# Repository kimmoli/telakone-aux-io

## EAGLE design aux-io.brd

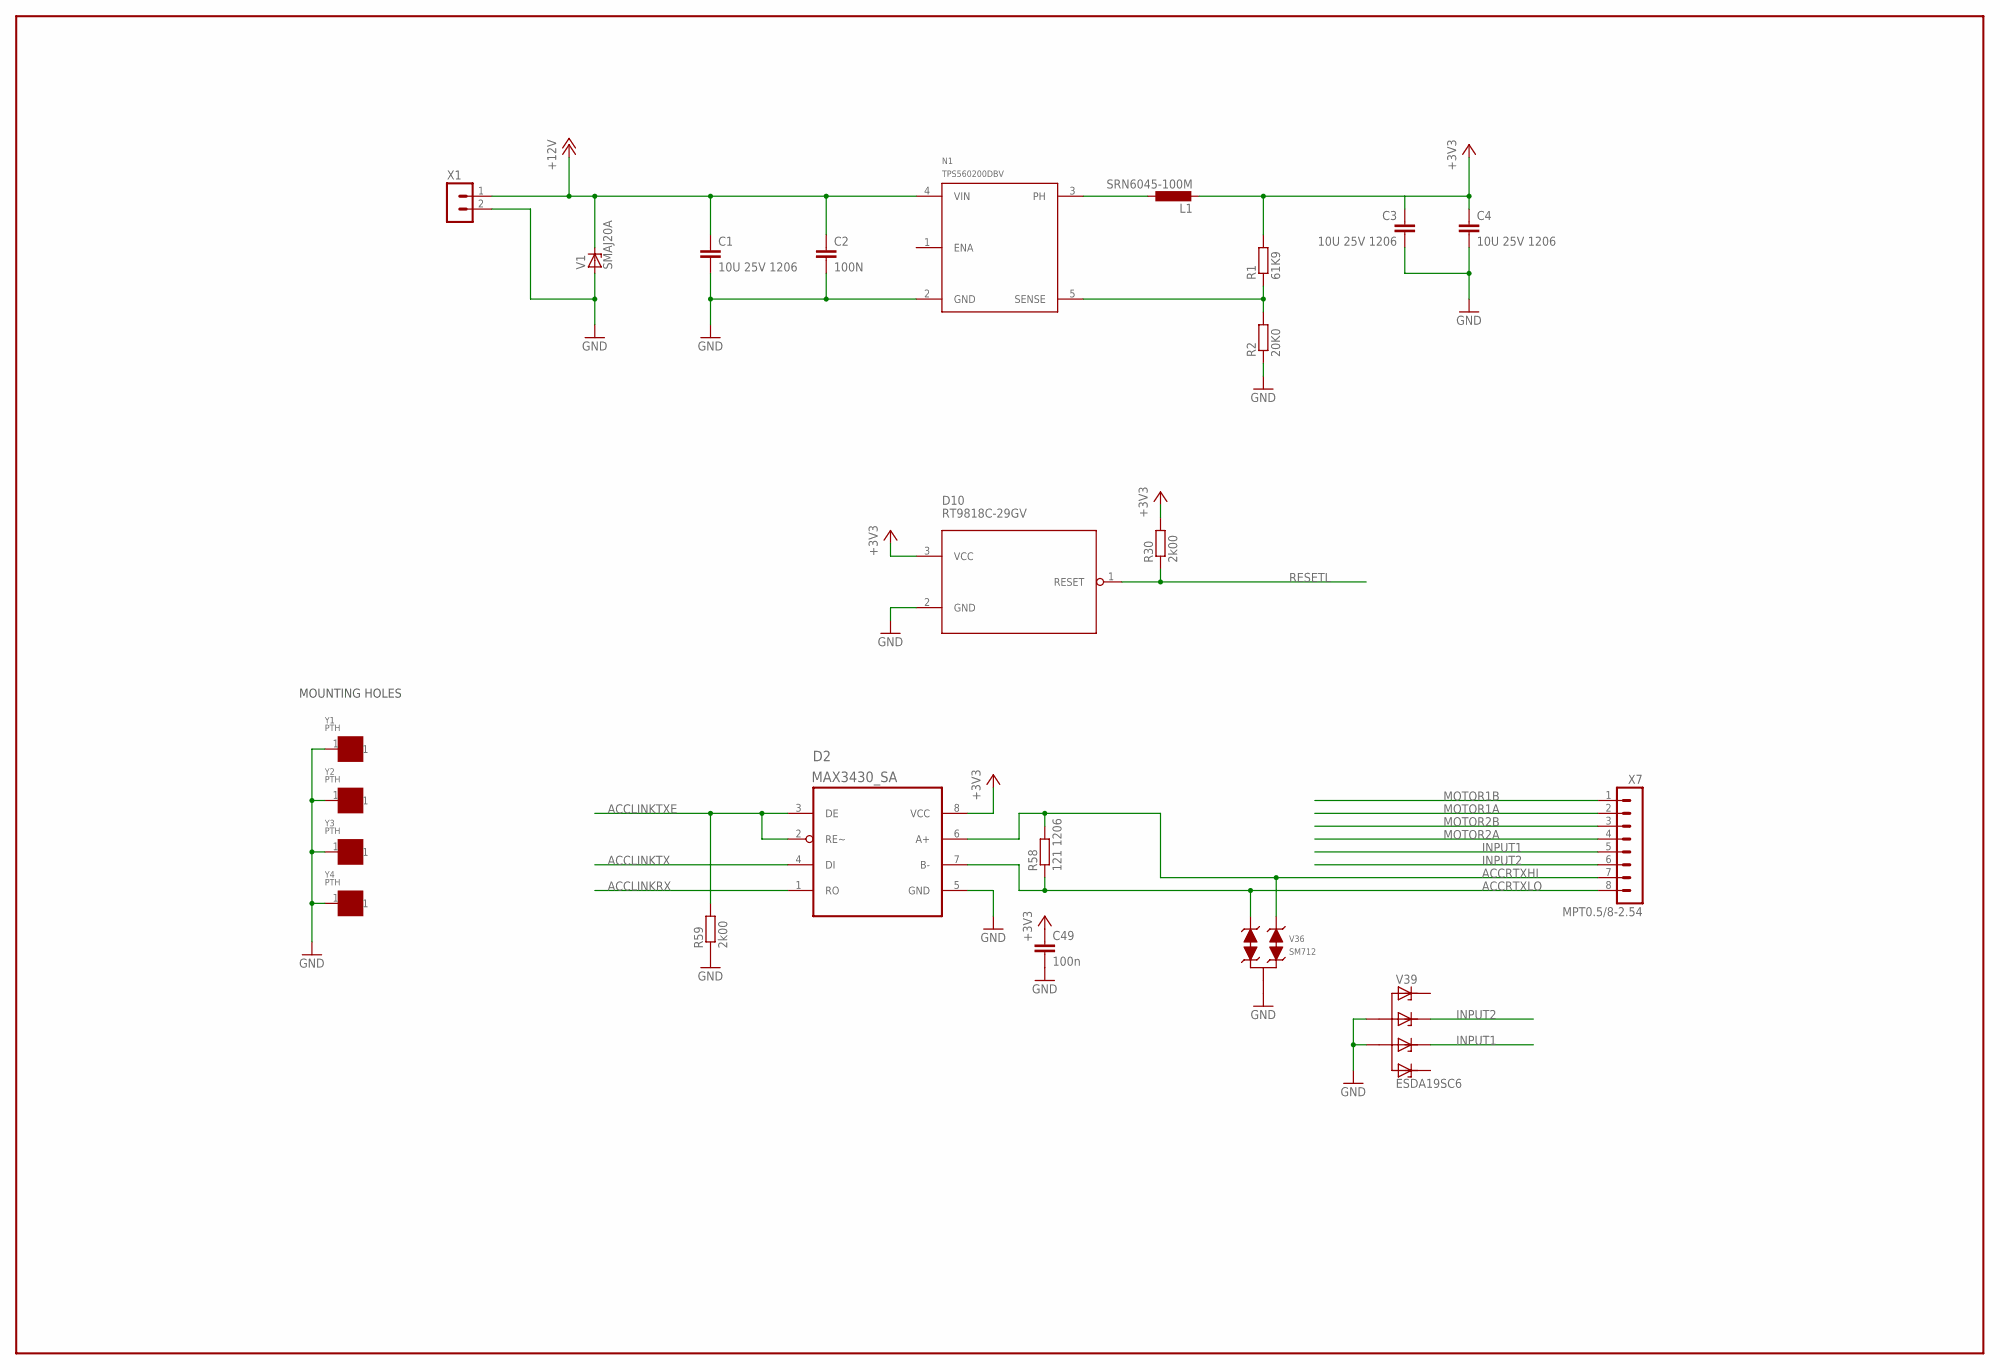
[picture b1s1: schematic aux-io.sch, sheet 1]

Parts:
C1, C3, C4: 10U 25V 1206; C1206
C2: 100N; C0603
C49: 100n; C0603
D2: MAX3430_SA; SOIC8-N_MC
D10: RT9818C-29GV; SOT23
L1: SRN6045-100M; SRN6045
N1: TPS560200DBV; SOT95P280X145-5N
R1: 61K9; R0603
R2: 20K0; R0603
R30, R59: 2k00; R0603
R58: 121 1206; R1206
V1: SMAJ20A; DO214AC
V36: SM712; SOT23
V39: ESDA19SC6; SOT23-6
X1: TE_RUUVILIITIN2
X7: MPT0.5/8-2.54
Y1, Y2, Y3, Y4: PTH; PTH-3.2-6DIA

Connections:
+3V3: C3.1, C4.1, C49.1, D2.8 (VCC), D10.3 (VCC), L1.2, R1.2, R30.2; also elsewhere on the board
+12V: C1.1, C2.1, N1.4 (VIN), V1.C, X1.1; also elsewhere on the board
ACCLINKRX: D2.1 (RO); also elsewhere on the board
ACCLINKTX: D2.4 (DI); also elsewhere on the board
ACCLINKTXE: D2.2 (RE~), D2.3 (DE), R59.2; also elsewhere on the board
ACCRTXHI: D2.6 (A+), R58.2, V36.1, X7.7
ACCRTXLO: D2.7 (B-), R58.1, V36.2, X7.8
GND: C1.2, C2.2, C3.2, C4.2, C49.2, D2.5 (GND), D10.2 (GND), N1.2 (GND), R2.1, R59.1, V1.A, V36.3, V39.2 (A), V39.5 (A1), X1.2, Y1.1, Y2.1, Y3.1, Y4.1; also elsewhere on the board
INPUT1: V39.4 (C2), X7.5; also elsewhere on the board
INPUT2: V39.3 (C1), X7.6; also elsewhere on the board
MOTOR1A: X7.2; also elsewhere on the board
MOTOR1B: X7.1; also elsewhere on the board
MOTOR2A: X7.4; also elsewhere on the board
MOTOR2B: X7.3; also elsewhere on the board
unnamed: L1.1, N1.3 (PH)
unnamed: N1.5 (SENSE), R1.1, R2.2
RESETL: D10.1 (RESET), R30.1; also elsewhere on the board

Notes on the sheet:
MOUNTING HOLES

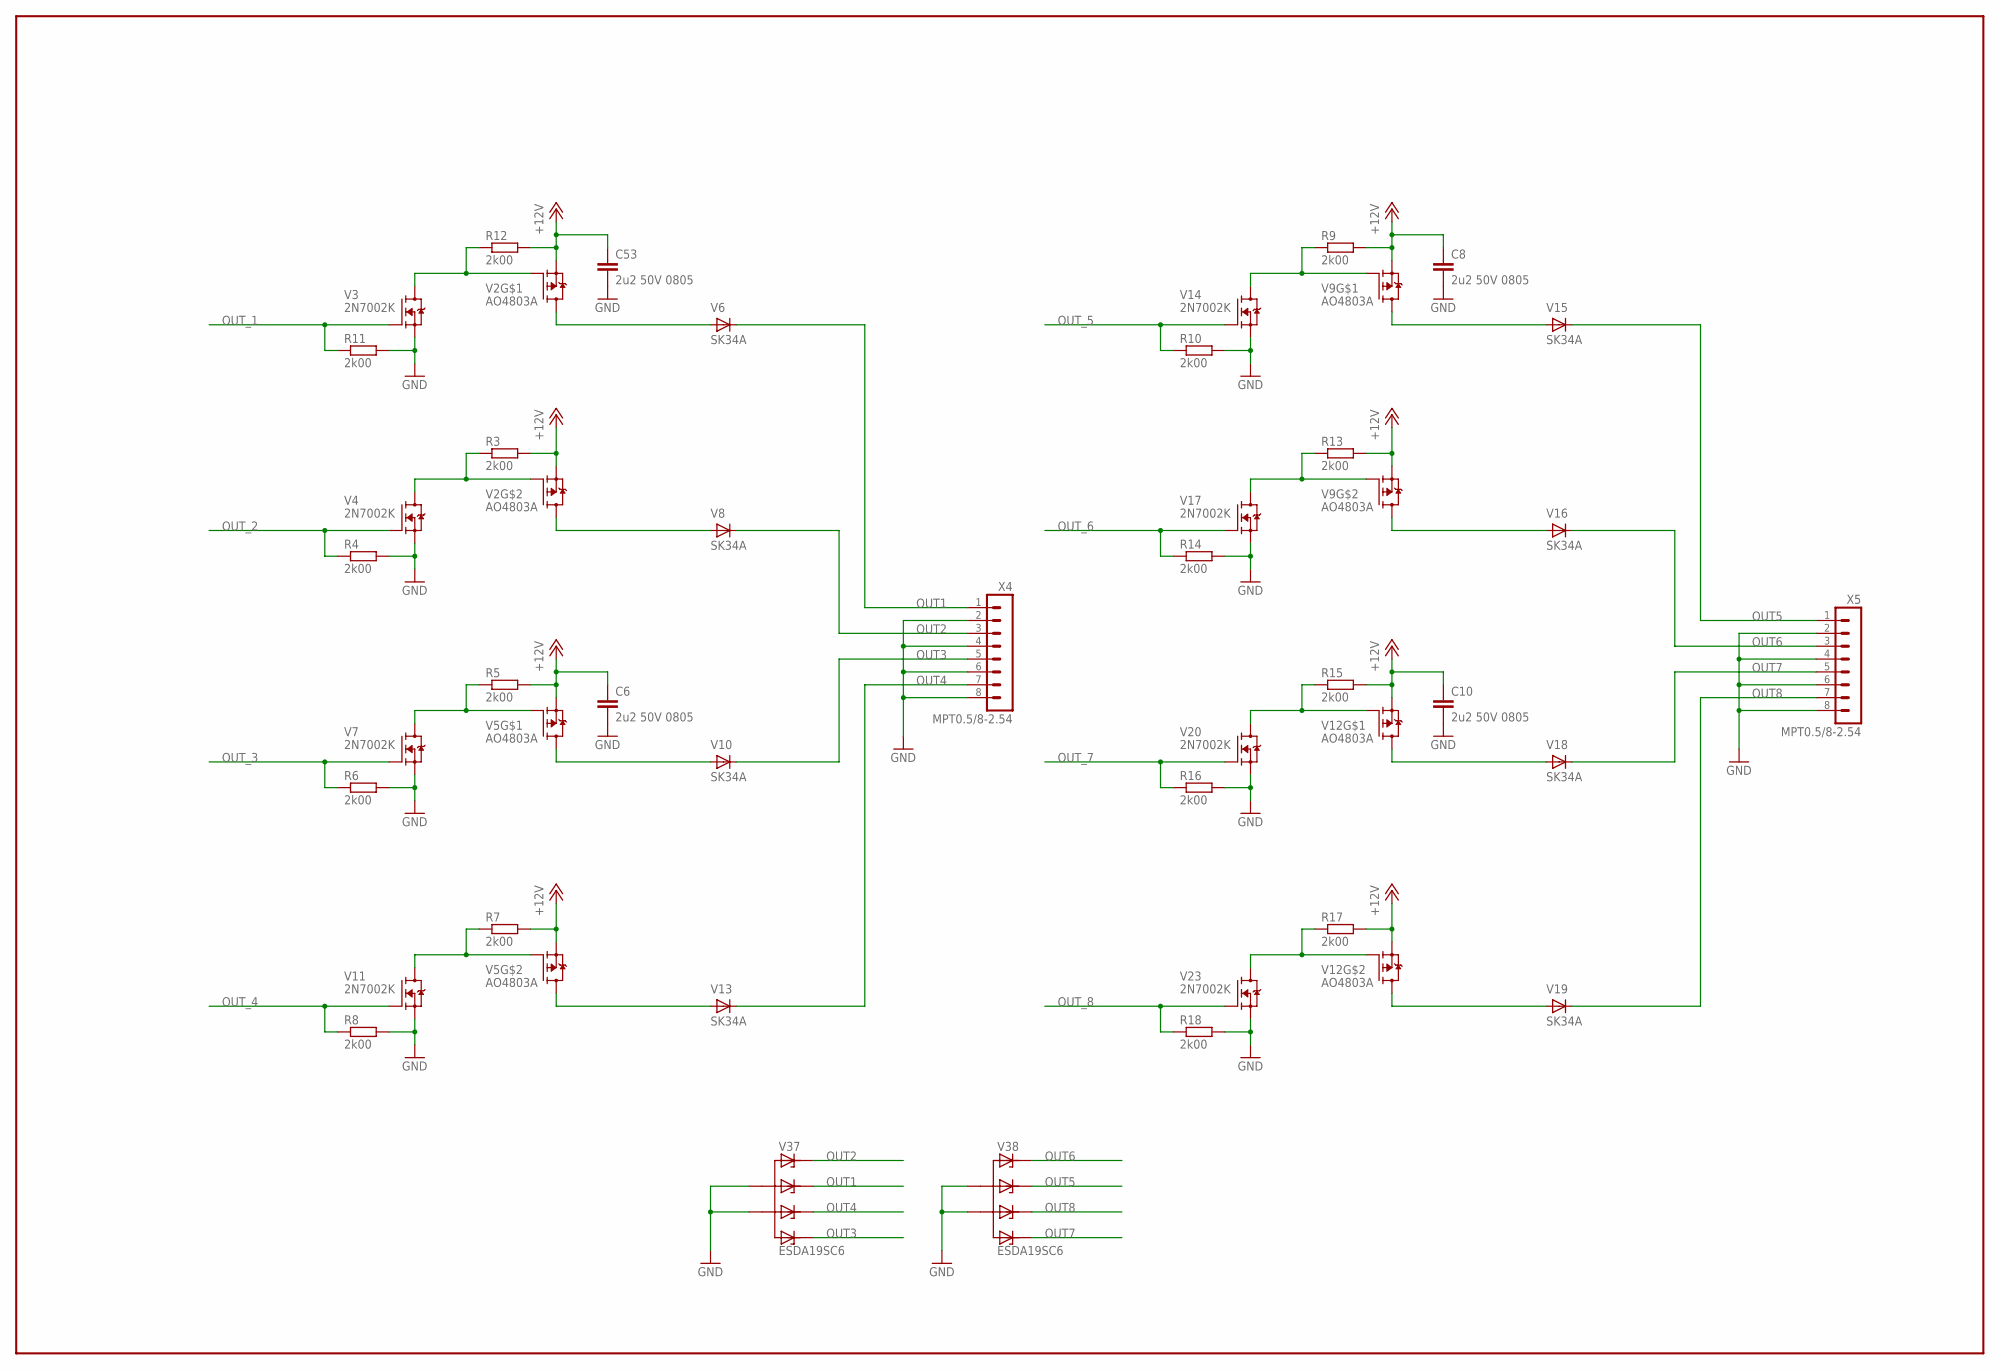
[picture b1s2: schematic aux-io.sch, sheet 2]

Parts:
C6, C8, C10, C53: 2u2 50V 0805; C0805
R3, R4, R5, R6, R7, R8, R9, R10, R11, R12, R13, R14, R15, R16, R17, R18: 2k00; R0603
V2, V5, V9, V12: AO4803A; SOIC8-N_MC
V3, V4, V7, V11, V14, V17, V20, V23: 2N7002K; SOT23
V6, V8, V10, V13, V15, V16, V18, V19: SK34A; DO214AC
V37, V38: ESDA19SC6; SOT23-6
X4, X5: MPT0.5/8-2.54

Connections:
+12V: C6.1, C8.1, C10.1, C53.1, R3.2, R5.2, R7.2, R9.2, R12.2, R13.2, R15.2, R17.2, V2.1 (S), V2.3 (S), V5.1 (S), V5.3 (S), V9.1 (S), V9.3 (S), V12.1 (S), V12.3 (S); also elsewhere on the board
GND: C6.2, C8.2, C10.2, C53.2, R4.2, R6.2, R8.2, R10.2, R11.2, R14.2, R16.2, R18.2, V3.2 (S), V4.2 (S), V7.2 (S), V11.2 (S), V14.2 (S), V17.2 (S), V20.2 (S), V23.2 (S), V37.2 (A), V37.5 (A1), V38.2 (A), V38.5 (A1), X4.2, X4.4, X4.6, X4.8, X5.2, X5.4, X5.6, X5.8; also elsewhere on the board
unnamed: R3.1, V2.2 (G), V4.3 (D)
unnamed: R5.1, V5.4 (G), V7.3 (D)
unnamed: R7.1, V5.2 (G), V11.3 (D)
unnamed: R9.1, V9.4 (G), V14.3 (D)
unnamed: R13.1, V9.2 (G), V17.3 (D)
unnamed: R15.1, V12.4 (G), V20.3 (D)
unnamed: R17.1, V12.2 (G), V23.3 (D)
unnamed: R12.1, V2.4 (G), V3.3 (D)
NERT: V2.5 (D), V2.6 (D), V6.A
NERT1: V2.7 (D), V2.8 (D), V8.A
NERT2: V5.5 (D), V5.6 (D), V10.A
NERT3: V5.7 (D), V5.8 (D), V13.A
NERT4: V9.5 (D), V9.6 (D), V15.A
NERT5: V9.7 (D), V9.8 (D), V16.A
NERT6: V12.5 (D), V12.6 (D), V18.A
NERT7: V12.7 (D), V12.8 (D), V19.A
OUT1: V6.C, V37.3 (C1), X4.1
OUT2: V8.C, V37.1 (C), X4.3
OUT3: V10.C, V37.6 (C3), X4.5
OUT4: V13.C, V37.4 (C2), X4.7
OUT5: V15.C, V38.3 (C1), X5.1
OUT6: V16.C, V38.1 (C), X5.3
OUT7: V18.C, V38.6 (C3), X5.5
OUT8: V19.C, V38.4 (C2), X5.7
OUT_1: R11.1, V3.1 (G); also elsewhere on the board
OUT_2: R4.1, V4.1 (G); also elsewhere on the board
OUT_3: R6.1, V7.1 (G); also elsewhere on the board
OUT_4: R8.1, V11.1 (G); also elsewhere on the board
OUT_5: R10.1, V14.1 (G); also elsewhere on the board
OUT_6: R14.1, V17.1 (G); also elsewhere on the board
OUT_7: R16.1, V20.1 (G); also elsewhere on the board
OUT_8: R18.1, V23.1 (G); also elsewhere on the board

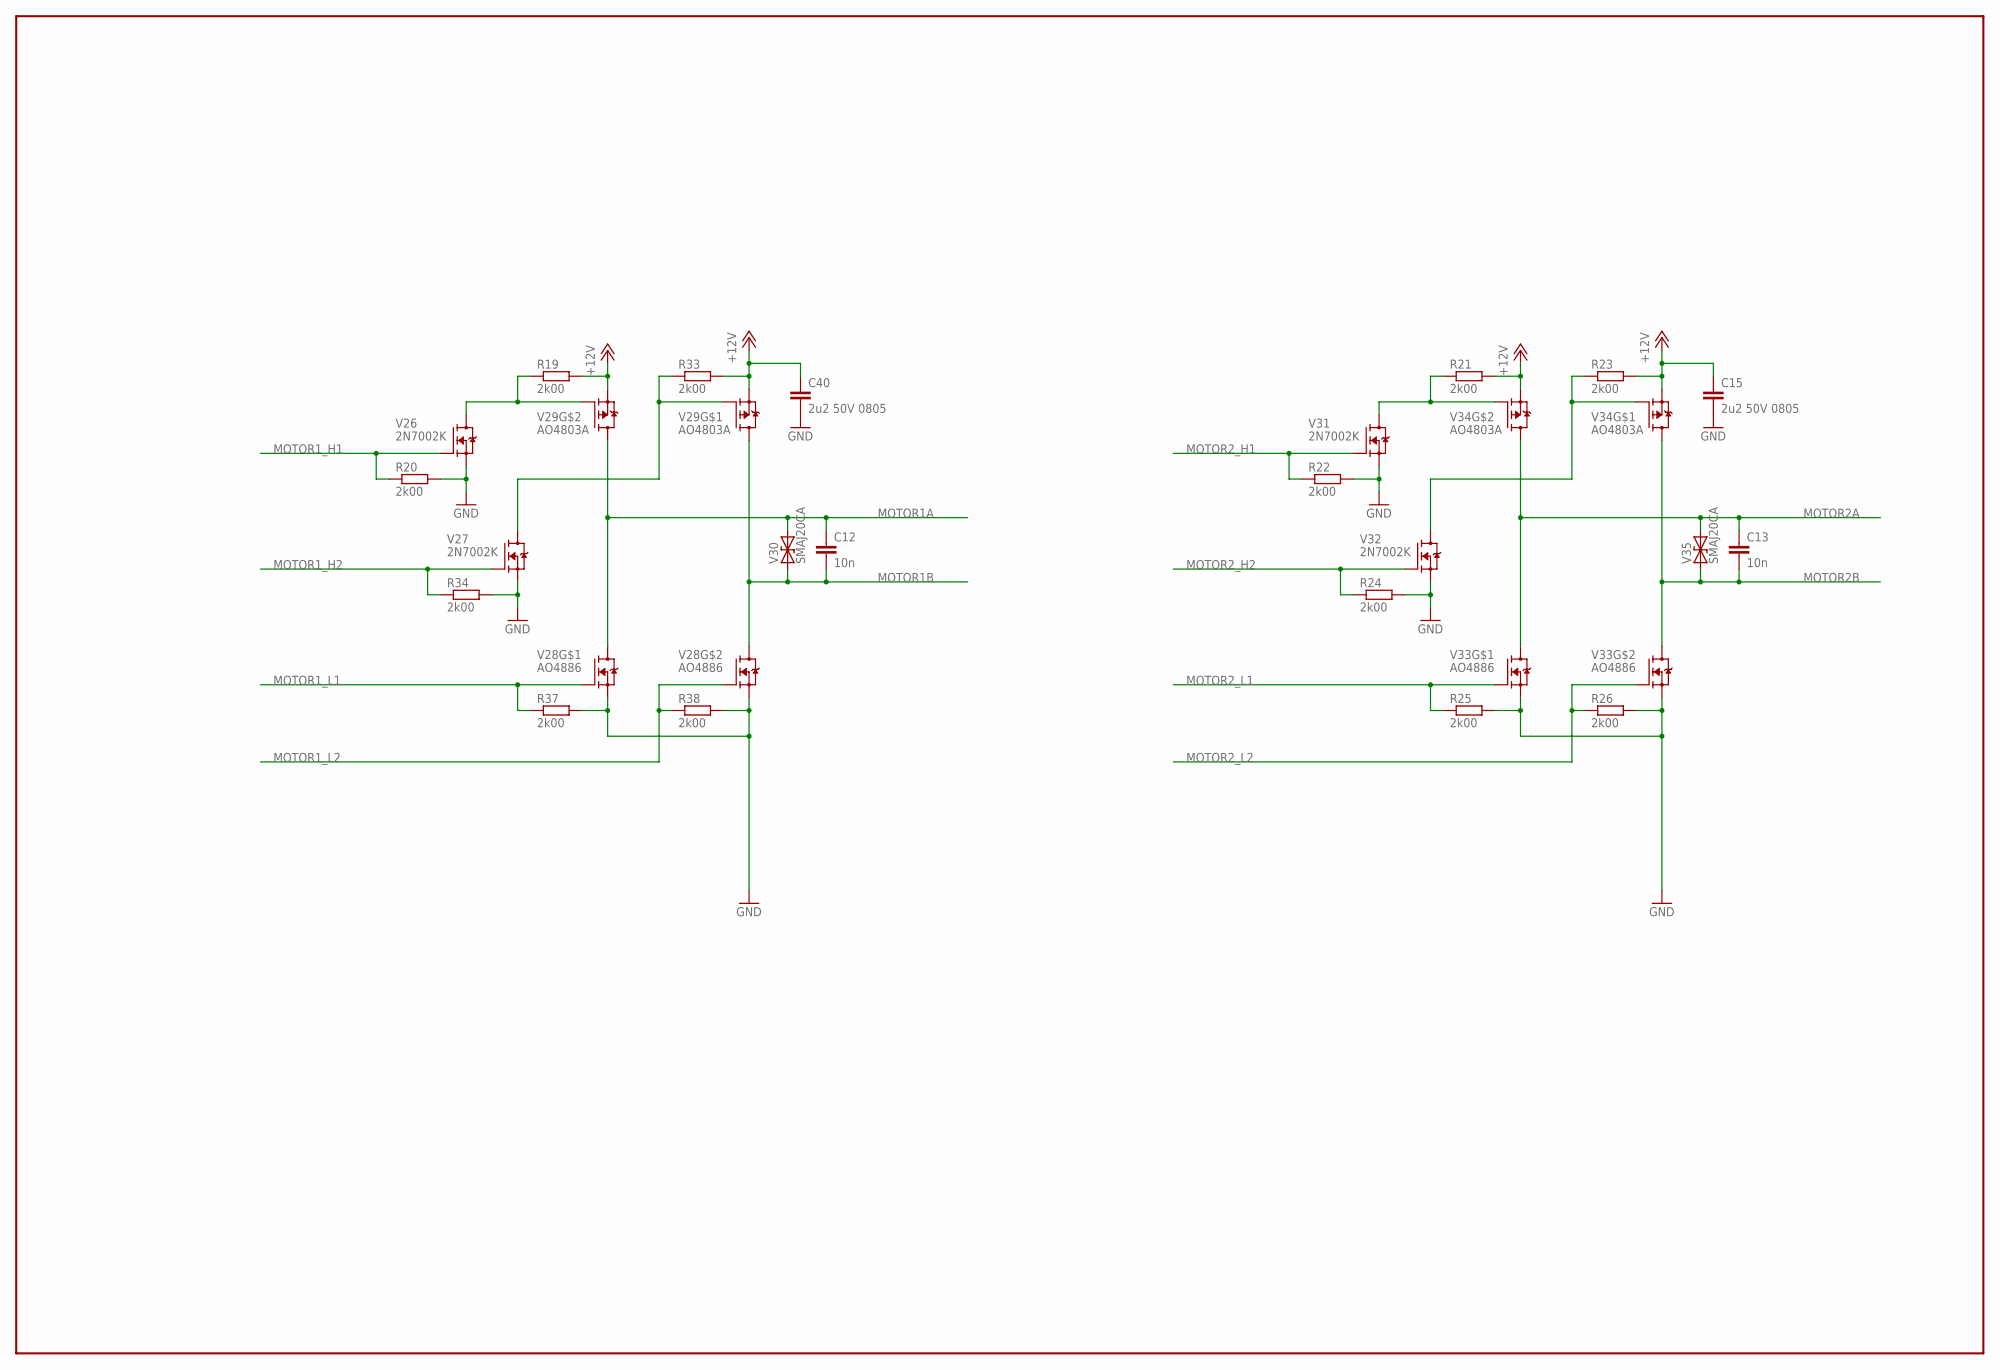
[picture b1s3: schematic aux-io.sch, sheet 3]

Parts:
C12, C13: 10n; C0603
C15, C40: 2u2 50V 0805; C0805
R19, R20, R21, R22, R23, R24, R25, R26, R33, R34, R37, R38: 2k00; R0603
V26, V27, V31, V32: 2N7002K; SOT23
V28, V33: AO4886; SOIC8-N_MC
V29, V34: AO4803A; SOIC8-N_MC
V30, V35: SMAJ20CA; DO214AC

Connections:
+12V: C15.1, C40.1, R19.2, R21.2, R23.2, R33.2, V29.1 (S), V29.3 (S), V34.1 (S), V34.3 (S); also elsewhere on the board
GND: C15.2, C40.2, R20.2, R22.2, R24.2, R25.2, R26.2, R34.2, R37.2, R38.2, V26.2 (S), V27.2 (S), V28.1 (S), V28.3 (S), V31.2 (S), V32.2 (S), V33.1 (S), V33.3 (S); also elsewhere on the board
MOTOR1A: C12.1, V28.5 (D), V28.6 (D), V29.7 (D), V29.8 (D), V30.A (2); also elsewhere on the board
MOTOR1B: C12.2, V28.7 (D), V28.8 (D), V29.5 (D), V29.6 (D), V30.C (1); also elsewhere on the board
MOTOR1_H1: R20.1, V26.1 (G); also elsewhere on the board
MOTOR1_H2: R34.1, V27.1 (G); also elsewhere on the board
MOTOR1_L1: R37.1, V28.4 (G); also elsewhere on the board
MOTOR1_L2: R38.1, V28.2 (G); also elsewhere on the board
MOTOR2A: C13.1, V33.5 (D), V33.6 (D), V34.7 (D), V34.8 (D), V35.A (2); also elsewhere on the board
MOTOR2B: C13.2, V33.7 (D), V33.8 (D), V34.5 (D), V34.6 (D), V35.C (1); also elsewhere on the board
MOTOR2_H1: R22.1, V31.1 (G); also elsewhere on the board
MOTOR2_H2: R24.1, V32.1 (G); also elsewhere on the board
MOTOR2_L1: R25.1, V33.4 (G); also elsewhere on the board
MOTOR2_L2: R26.1, V33.2 (G); also elsewhere on the board
unnamed: R19.1, V26.3 (D), V29.2 (G)
unnamed: R33.1, V27.3 (D), V29.4 (G)
unnamed: R21.1, V31.3 (D), V34.2 (G)
unnamed: R23.1, V32.3 (D), V34.4 (G)

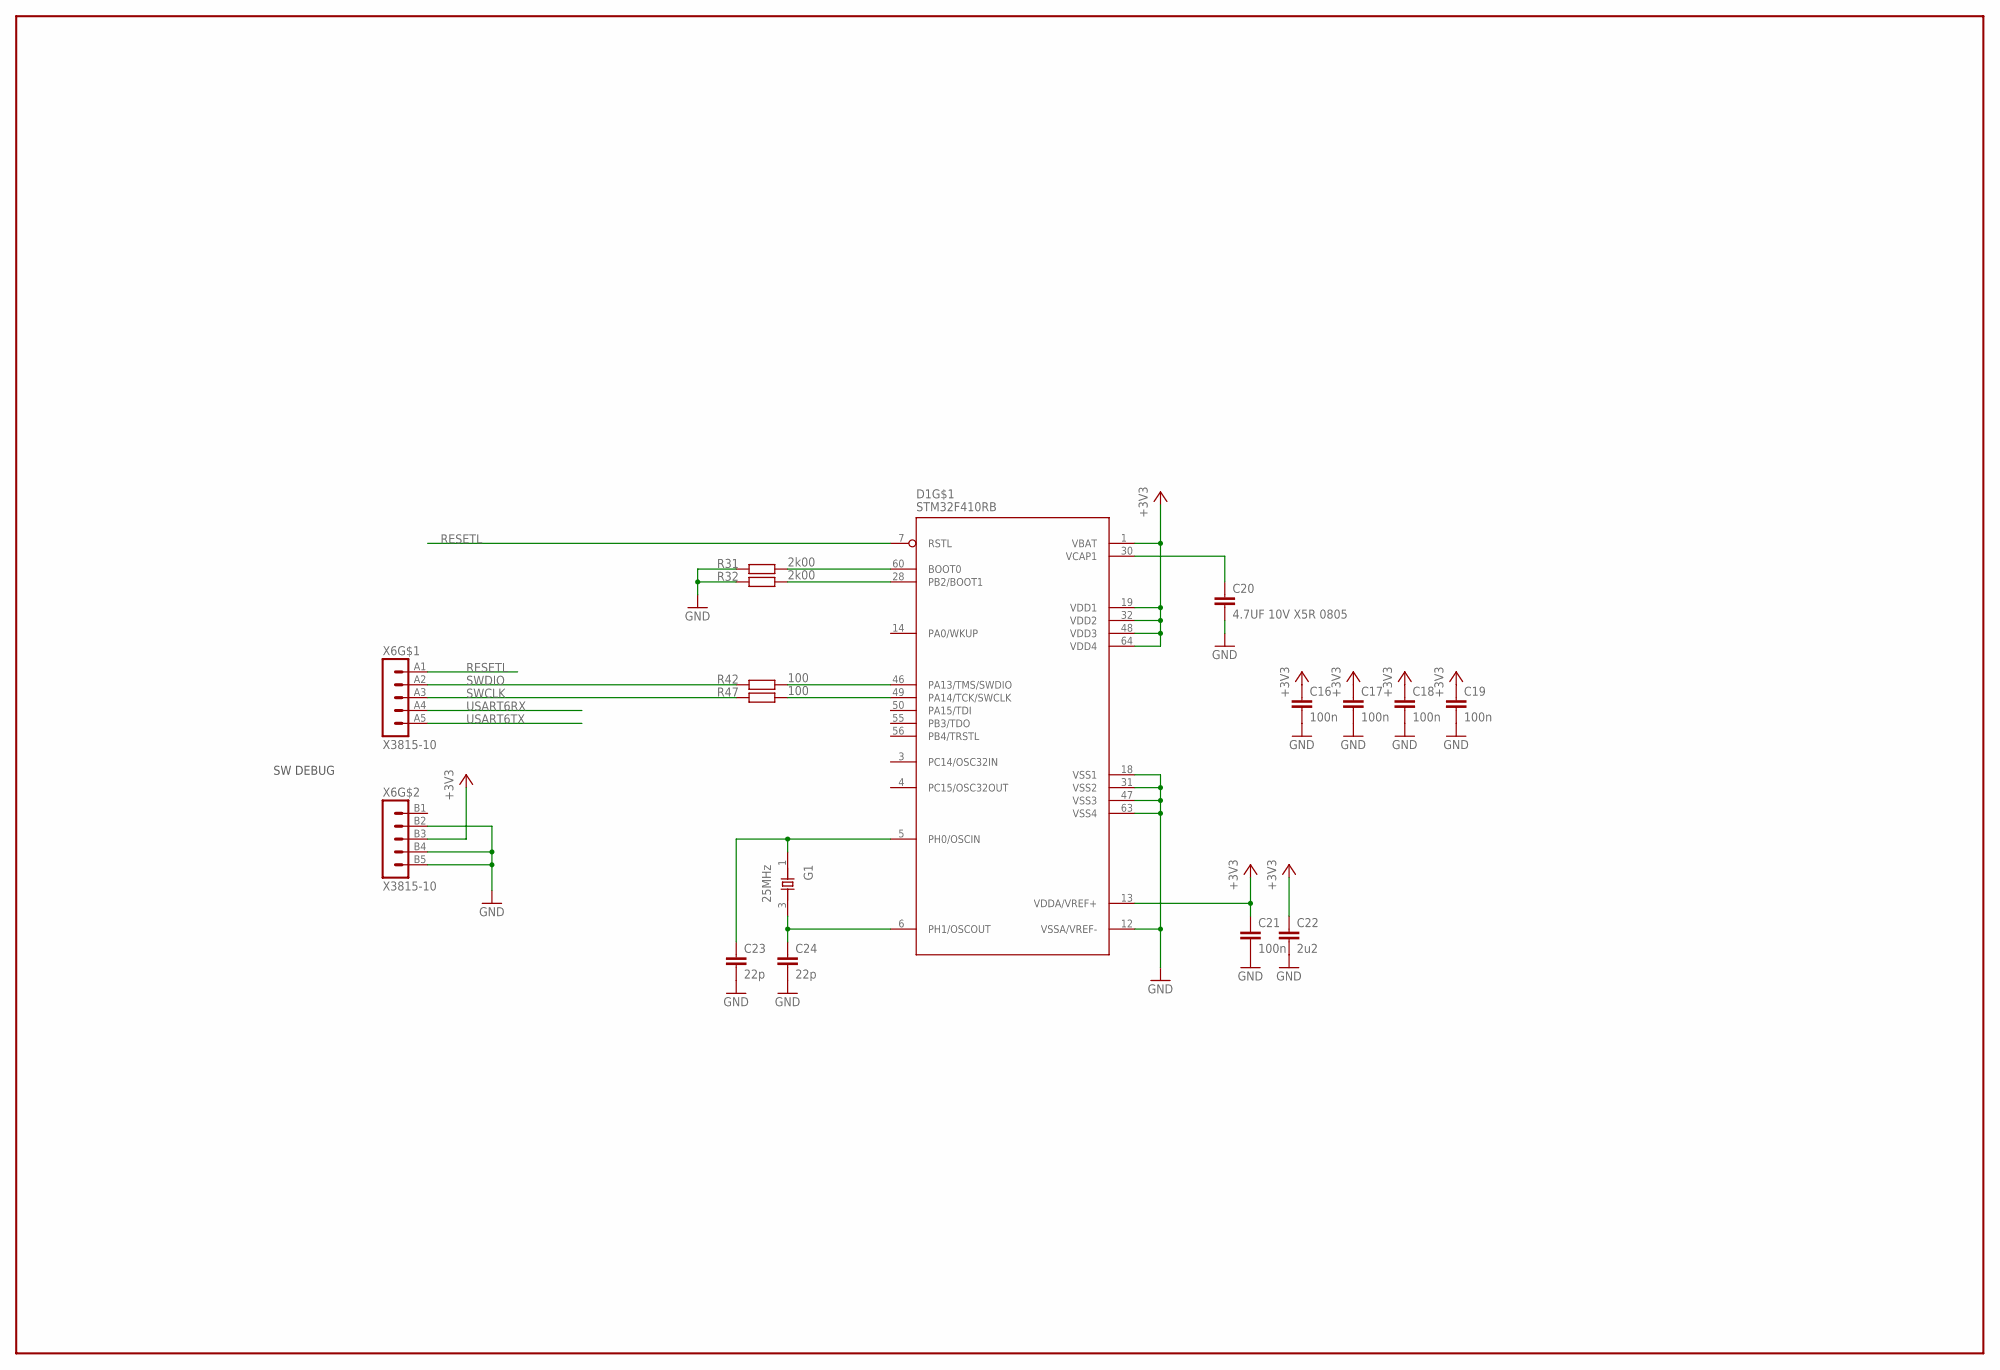
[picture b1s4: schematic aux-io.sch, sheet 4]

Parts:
C16, C17, C18, C19, C21: 100n; C0603
C20: 4.7UF 10V X5R 0805; C0805
C22: 2u2; C0603
C23, C24: 22p; C0603
D1: STM32F410RB; LQFP-64
G1: 25MHz; X_3225
R31, R32: 2k00; R0603
R42, R47: 100; R0603
X6: X3815-10; 15110102601

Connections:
+3V3: C16.1, C17.1, C18.1, C19.1, C21.1, C22.1, D1.1 (VBAT), D1.13 (VDDA/VREF+), D1.19 (VDD1), D1.32 (VDD2), D1.48 (VDD3), D1.64 (VDD4), X6.B3 (3); also elsewhere on the board
BOOT0: D1.60 (BOOT0), R31.2
BOOT1: D1.28 (PB2/BOOT1), R32.2
GND: C16.2, C17.2, C18.2, C19.2, C20.2, C21.2, C22.2, C23.2, C24.2, D1.12 (VSSA/VREF-), D1.18 (VSS1), D1.31 (VSS2), D1.47 (VSS3), D1.63 (VSS4), R31.1, R32.1, X6.B2 (2), X6.B4 (4), X6.B5 (5); also elsewhere on the board
OSCIN: C23.1, D1.5 (PH0/OSCIN), G1.1 (X1)
OSCOUT: C24.1, D1.6 (PH1/OSCOUT), G1.3 (X2)
RESETL: D1.7 (RSTL), X6.A1 (1); also elsewhere on the board
SWCLK: R47.1, X6.A3 (3)
SWCLK_CPU: D1.49 (PA14/TCK/SWCLK), R47.2
SWDIO: R42.1, X6.A2 (2)
SWDIO_CPU: D1.46 (PA13/TMS/SWDIO), R42.2
USART6RX: X6.A4 (4); also elsewhere on the board
USART6TX: X6.A5 (5); also elsewhere on the board
VCAP1: C20.1, D1.30 (VCAP1)

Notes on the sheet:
SW DEBUG

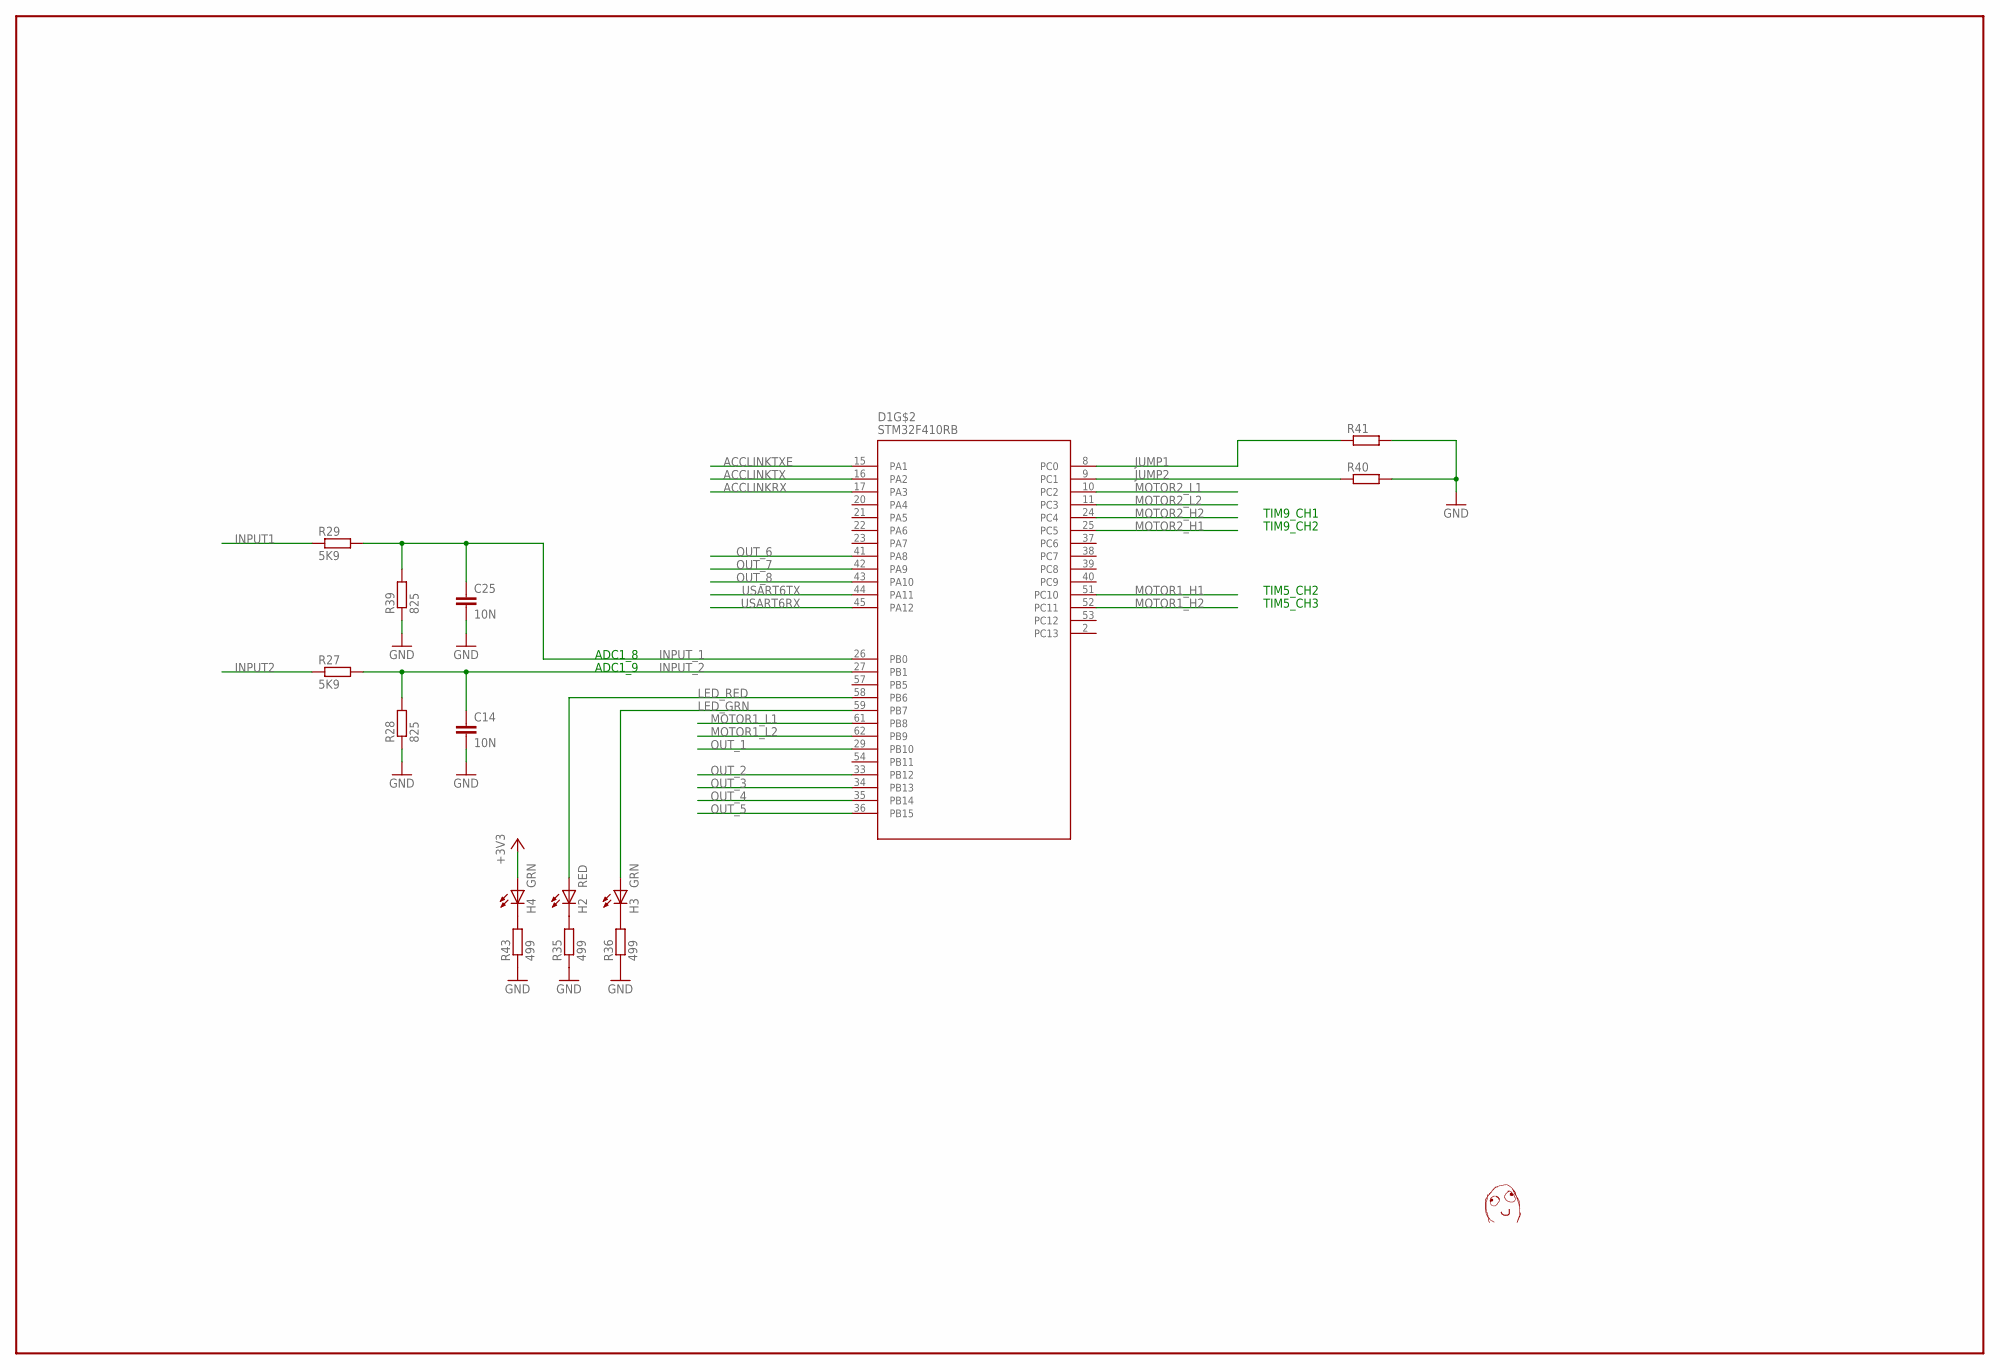
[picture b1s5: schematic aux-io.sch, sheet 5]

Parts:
C14, C25: 10N; C0603
D1: STM32F410RB; LQFP-64
H2: RED; CHIP-LED0603
H3, H4: GRN; CHIP-LED0603
R27, R29: 5K9; R1206
R28, R39: 825; R0603
R35, R36, R43: 499; R0603
R40, R41: RES0603; R0603
U$1: DAFUG

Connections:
+3V3: H4.A; also elsewhere on the board
ACCLINKRX: D1.17 (PA3); also elsewhere on the board
ACCLINKTX: D1.16 (PA2); also elsewhere on the board
ACCLINKTXE: D1.15 (PA1); also elsewhere on the board
GND: C14.2, C25.2, R28.1, R35.1, R36.1, R39.1, R40.2, R41.2, R43.1; also elsewhere on the board
INPUT1: R29.1; also elsewhere on the board
INPUT2: R27.1; also elsewhere on the board
INPUT_1: C25.1, D1.26 (PB0), R29.2, R39.2
INPUT_2: C14.1, D1.27 (PB1), R27.2, R28.2
JUMP1: D1.8 (PC0), R41.1
JUMP2: D1.9 (PC1), R40.1
LED_GRN: D1.59 (PB7), H3.A
LED_RED: D1.58 (PB6), H2.A
MOTOR1_H1: D1.51 (PC10); also elsewhere on the board
MOTOR1_H2: D1.52 (PC11); also elsewhere on the board
MOTOR1_L1: D1.61 (PB8); also elsewhere on the board
MOTOR1_L2: D1.62 (PB9); also elsewhere on the board
MOTOR2_H1: D1.25 (PC5); also elsewhere on the board
MOTOR2_H2: D1.24 (PC4); also elsewhere on the board
MOTOR2_L1: D1.10 (PC2); also elsewhere on the board
MOTOR2_L2: D1.11 (PC3); also elsewhere on the board
unnamed: H3.C, R36.2
unnamed: H2.C, R35.2
unnamed: H4.C, R43.2
OUT_1: D1.29 (PB10); also elsewhere on the board
OUT_2: D1.33 (PB12); also elsewhere on the board
OUT_3: D1.34 (PB13); also elsewhere on the board
OUT_4: D1.35 (PB14); also elsewhere on the board
OUT_5: D1.36 (PB15); also elsewhere on the board
OUT_6: D1.41 (PA8); also elsewhere on the board
OUT_7: D1.42 (PA9); also elsewhere on the board
OUT_8: D1.43 (PA10); also elsewhere on the board
USART6RX: D1.45 (PA12); also elsewhere on the board
USART6TX: D1.44 (PA11); also elsewhere on the board

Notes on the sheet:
TIM9_CH1
TIM9_CH2
TIM5_CH2
TIM5_CH3
ADC1_9
ADC1_8

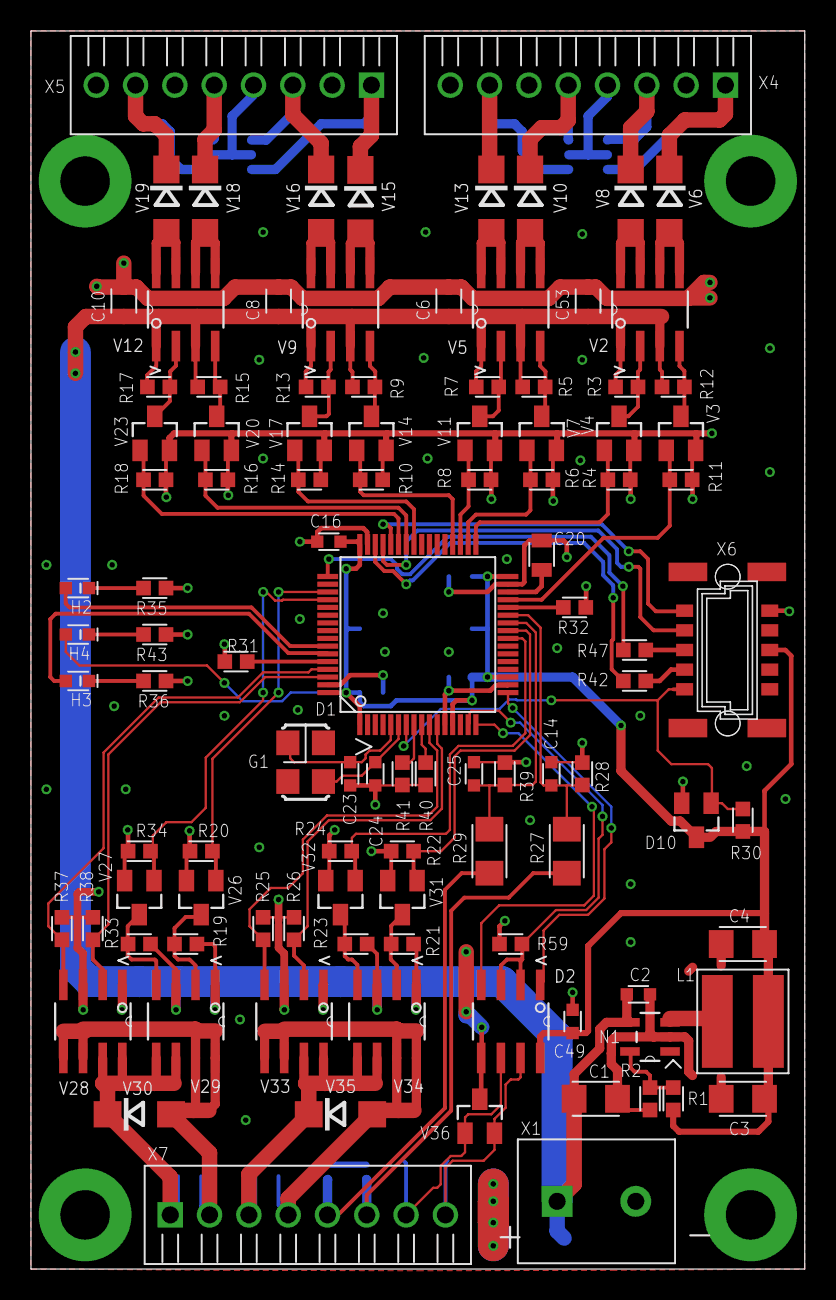
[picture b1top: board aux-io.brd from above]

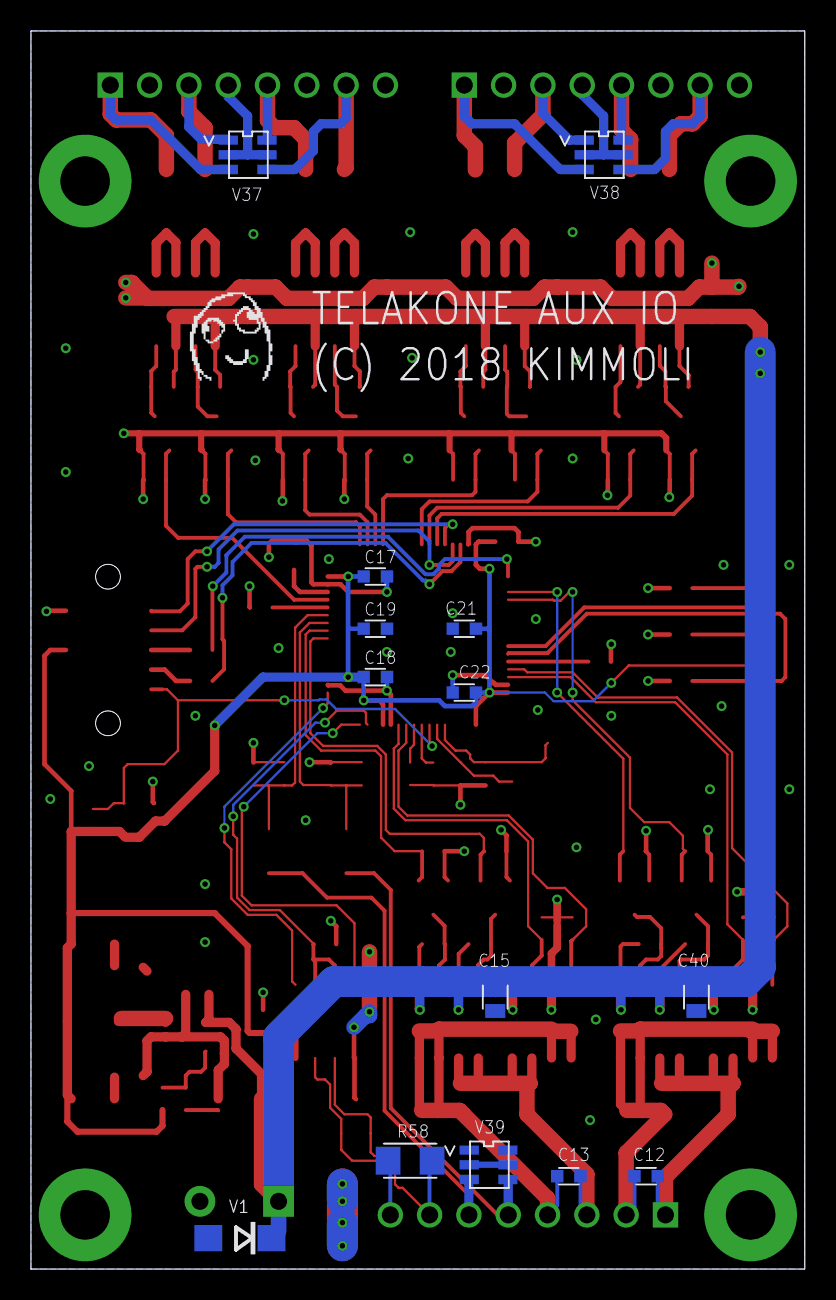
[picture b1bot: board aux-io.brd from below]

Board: 2 copper layers, 50.0 x 80.0 mm, 125 parts (15 on the bottom side), 81 nets.

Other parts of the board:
DRILEGEND: DRILEGEND

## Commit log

2018-11-25 initial
2018-11-25 routed
2018-11-26 iomap
2018-11-26 assembly drawing

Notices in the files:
aux-io.brd:
(C) 2018 KIMMOLI
